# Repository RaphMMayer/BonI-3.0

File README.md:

# BonI 3.0
Mobile platform for sensory feedback via bone conduction.

The Project gives the PCB, Embedded SW and the API to drive the device via Bluetooth/Wifi.
## Table of Content
* [The PCB](#the-pcb)
  * [Two Layer PCB](#two-layer-pcb)
    * [Components](#components)
    * [Modifications](#modifications)
    * [Connection of the PCB](#connection-of-the-pcb)
    * [Programming and Operation of the PCB](#programming-and-operation-of-the-pcb)
    * [Debugging of the PCB](#debugging-of-the-pcb)
    * [Files](#files)
  * [Four Layer PCB](#four-layer-pcb)
  
* [Schematic](#schematic)
  * [The MCU](#the-mcu)
    * [MCU Pin Connections](#mcu-pin-connections)
  * [Frequency Generator](#frequency-generator)
    * [Frequency Generator Pin Connections](#frequency-generator-pin-connections)
    * [Programming the Frequency Generator](#programming-the-frequency-generator)

## The PCB
### Two Layer PCB:
The two layer PCB is designed as a prototype to our system. The PCB is a two layer board with a poured common ground on the bottom plane for both analogue and digital circuitry. Power traces and signal traces are located mostly on the top plane. With two mounting holes at the side of the PCB it is intended to be contained in the designed box. The PCB is fabricated and assembled by PCBWay.
#### Components:
- A power supply that can regulate 5V input into 3.3V and 5V. The 5V can be sourced from the programmer pins.
- ESP32 as the microcontorller.
- Three AD5932 ICs to generate frequencies.
- Three AD5970 digital potentiometers ICs for controlling the amplitude. 
- Three NCS2211 class AB amplifier ICs.
#### Modifications:
Being the first prototype of our project the PCB is heavily modified.
In order for the PCB to operate normally:
- The unconnected side of resistor C1 needs to be connected to ground.
- One of the unconnected pins of SW1 needs to be connected to ground.
- upper pads of C14 and C15 needs to be connected to provide power to function generators.
- R7, R11, R15, R19, R22 and R25 needs to be desoldered for the correct operation of SPI communications.
- 20K 0402 resistors need to be soldered at R20, R23 and R26 for the amplifier to work.
- The USB footprint J1 is left unused and is not intended to be used.
- Solder 2.56mm connecters to top pin of J1 and the square pin of J1, they are respectively the ground and +5 power supply for the PCB.
#### Connection of the PCB:
The PCB uses 2.56mm connectors for its programming pins and transducer signal output. 2.56mm female jumper headers should be used for proper connection to the system.
The battery port uses standard JST connenctors to fit with most lithium ion batteries.
#### Programming and Operation of the PCB:
The prototype is programmed with Arduino IDE. To program the PCB properly, the following instructions must be followed:
1. Connect TP12 and TP18 to ground. This allows ESP32 to be working in bootloading mode and allows for 3.3V flashing voltage. Failing to do so will result in flash read error.
2. Set the uploading speed to 115200 or above, it will not work with 921600.
3. When uploading the code press and hold SW2, wait until `connecting....`shows up, press and release SW1. This put ESP into flashing mode. Failing to do so will result in `A fatal error occurred: Failed to connect to ESP32: Timed out waiting for packet header`.
4. When it is uploading the code SW2 can now be released.
5. After uploading, `Hard resetting via RTS pin` should be observed,press the SW1 again to reset and boot the program. 
6. Now TP12 and TP18 can be lifted from ground to allow the pins from the MCU to operate as normal I/O pins, but TP18 should be connected to ground when trying to reboot the MCU.
#### Debugging of the PCB:
If encountered any problem, test points near the MCU are available for ruling out errors and faulty circuits.
| Test Point No. |  Net Name | Description |
|----|----|----|
|TP1|CTRL3| The transition from low to high at this pin enable the output of bottom function generator after it being reprogrammed |
|TP2|STANDBY3| Toggle to high to disable the bottom function generator|
|TP3|CTRL2| The transition from low to high at this pin enable the output of middle function generator after it being reprogrammed |
|TP4|CTRL1| The transition from low to high at this pin enable the output of top function generator after it being reprogrammed|
|TP5|STANDBY1|Toggle to high to disable the top function generator|
|TP6|STANDBY2|Toggle to high to disable the middle function generator|
|TP7|SPI1CLK|This pin should provide the clock to all the SPI devices|
|TP8|No connection|Don't Bother|
|TP9|ENABLE1|Toggle to high to turn off the top amplifier(May not work)|
|TP10|ENABLE2|Toggle to high to turn off the middle amplifier(May not work)|
|TP11|SPI1MOSI|This pin should transmit data to all the SPI devices|
|TP12|FSYNC2| This is the slave select pin for the middle function generator, when toggled low it allows the middle function generator to receive data from the MCU|
|TP13|FSYNC3| This is the slave select pin for the bottom function generator, when toggled low it allows the bottom function generator to receive data from the MCU|
|TP14|ENABLE3| Toggle to high to turn off the bottom amplifier(May not work) |
|TP15|SYNC3|This is the slave select pin for the bottom digital potentiometer, when toggled low it allows the bottom digital potentiometer to receive data from the MCU|
|TP16|FSYNC1|This is the slave select pin for the top function generator, when toggled low it allows the top function generator to receive data from the MCU|
|TP17|SYNC1|This is the slave select pin for the top digital potentiometer, when toggled low it allows the top digital potentiometer to receive data from the MCU|
|TP18|SYNC2|This is the slave select pin for the middle digital potentiometer, when toggled low it allows the middle digital potentiometer to receive data from the MCU|
#### Files
All the PCB designs are done in KiCad. The PCB files of the two layer board can be found in the repository. The design is modified so that the aforementioned modifications does not need to be carried out for the two layer board PCB design if the desgin is to be printed in manufactures.
### Four Layer PCB
## Schematic
Both the original and updated version of the schematic can be found in the repository. The schematic is drawn in KiCad. On the first page, there is the frequency generator, amplifier and digital potentiometer. On the second page, there is the MCU and power section. 
### The MCU:
The MCU used in ths project is ESP32-WROOM-32D(4MB)([datasheet](https://www.espressif.com/sites/default/files/documentation/esp32-wroom-32_datasheet_en.pdf)). It mainly serves for communication between the GUI and the frequency generator. Apart from a few pins used for programming, most of the pins are used to communicate with the frequency generators, digital potentiometers and the amplifier.
The MCU communicates with frequency gnerators and digital potentiometers using SPI protocol. The ESP32 has two SPI channels available, and only one of them is utilized. Below are the connections from the MCU.
#### MCU Pin Connections
|Pin No.|Pin Name|Descriptions|
|----|----|----|
|1,15,38|GND|Connected to ground|
|2|DVDD|Power of ESP32, a well regulated 3.3V source is needed|
|3|EN|Reset pin of ESP32, it is connected to a switch, push to reboot the system|
|4|SENSOR_VP|Not used|
|5|SENSOR_VN|Not used|
|6,7,8|IO34 IO35 IO32|Not used|
|9,14,27|IO33 IO12 IO16|SYNC3, SYNC2 and SYNC1, slave select for digital potentiometer|
|10,16,28|IO25 IO13 IO17|ENABLE3, ENABLE2 and ENABLE1, used for turning on and off the amplifier|
|11,23,29|IO26 IO15 IO5|STANDBY3, STANDBY2 and STANDBY1, used for turning on and off the frequency generator|
|12,24,31|IO27 IO2 IO19|FSYNC3, FSYNC2 and FSYNC1, slave select for frequency generator|
|13,26,33|IO14 IO4 IO21|CTRL3, CTRL2 and CTRL1, update the output of the frequency generator|
|17,18,19,20,21,22|SDO SDI SHD SWP SCK SCS| Not used|
|25|IO0| Connected to a switch, hold low and press EN to enter bootloading|
|30|IO18|SPICLK used to synchronize all the SPI devices|
|32|NC|Do not connect|
|34,35|RXD0 TXD0| Serial port used for prgramming, connected to programming pins.|
|36|IO22|Not used.|
|37|IO23|SPIMOSI Used to send SPI data from the MCU|
### Frequency Generator
The frequency generator used in this project is AD5932([datasheet](https://www.analog.com/media/en/technical-documentation/data-sheets/AD5932.pdf)). This is a direct digital synthesis IC that uses SPI communication. It has 24 bits resolution frequency generation derived from the master clock (MCLK) fed in to it. In other words, the frequency it can output can be calculated by MCLK/2^24. We use a MCLK of 32.768kHz for our application. This means we have a frequency range from 0Hz to 32.768kHz with a frequency resolution of 0.00195Hz. It can produce sinusoidal, triangle and square waves at a fixed amplitude of 580 mV peak to peak. The IC also have auto frequency sweeping fucntion, which we are not intended to use in our project. To program the IC properly the MCU must write to AD5932 using SPI communication. 
#### Frequency Generator Pin Connections
|Pin No.|Pin Name|Descriptions|
|----|----|----|
|1|COMP|Decoupled to AVDD|
|2|AVDD|Analog supply (3.3V)|
|3|DVDD|Digital supply (3.3V)|
|4|CAP/2.5V|Decoupled to ground, decoupled to DVDD if DVDD is less than 2.5V|
|5|DGND|Digital Ground|
|6|MCLK|Input master clock from here, connected to SG-3030CM clock generator([datasheet](#https://www5.epsondevice.com/en/products/crystal_oscillator/sg3030cm.html))|
|7|SYNCOUT|Not connected, will output a signal after a frequency sweep(not tested)|
|8|MSBOUT|Not connected, square wave output can be yielded from this port|
|9|Interrupt|Not connected, used to interrupt a frequency sweep|
|10|CTRL|This pin needs to be toggled from low to high to output the frequency written to the frequency generator|
|11|SDATA|The MOSI pin of the device, receive data from SPI master|
|12|SCLK| The SPICLK pin of the device, receive clock from MCU to synchronize the bit transmision|
|13|FSYNC| The slave select pin of the device, pulled low to allow receiving of data|
|14|STANDY| Pull the pin high to disable the frequency generator|
|15|AGND|Analog ground|
|16|VOUT|The output pin for both triangle and sinusoidal wave, switch between the two in software|
#### Programming the Frequency Generator
To program the frequency generator AD5932, a 12 bit data must be written to the 4 bit register with mode 3 SPI communication(CPOL=1 CPHA=0). The following table shows the register used and the data transmitted to each register in the program where the first four bits represent the register written to and the rest are the data bits:
|Function|Data(Binary)|Data(Hexadecimal)|Description|
|--------|---|-----|---|
|Initialize:|	0	0	0	0 1 1 1 0	1 1	0	1	0	0	1	1|0x0ED3|	bit 11 set to one so that both	LSB and MSB are needed to change the outputfrequency. Bit 10 set to 1 to Enable DAC. Bit 9 set to 1	to select sinusoidal wave (0 for triangle wave).	Bit 8 set to 0 for N=no square output(1 for square output from MSBout)	Bit 5 set to 0 to enable automatic frequecny sweep(Don't matter). Bit 3 only matter if bit 2 is set to 1.	Bit 2 set to 0 to not have a pulse at end of sweep(not needed)|	
|No of increment|		0	0	0	1	0	0	0	0	0	0	0	0	0	0	1	0	|0x1002|The bit transmitted should be set to decimal equivalent of 2 for the minimum number of frequency increments(not needed in our case)|
|Period of increment|0	1	1	0	x	x	x	x	x	x	x	x	x	x	x	x|	0x63E8|	Don't care if no frequency sweeping is needed. It is initailized to 1000/MCLK=0.03s|
Frequency Increment LSB|0	0	1	0	0	0	0	0	0	0	0	0	0	0	0	0|0x2000|		Set to 0 if not needed|
Frequency Increment MSB|0	0	1	1	0	0	0	0	0	0	0	0	0	0	0	0	|0x3000|Set to 0 if not needed|																
Start Frequency LSB|1	1	0	0	0	0	0	0	0	0	0	0	0	0	0	0|0xC000|	Set the frequency output. Divide the desired frequency by 0.00195 to yield the data bits.|
Start Frequency MSB	|1	1	1	0	0	0	0	0	0	0	0	0	0	0	0	0|0xD000|Set the frequency output. Divide the desired frequency by 0.00195 to yield the data bits.|

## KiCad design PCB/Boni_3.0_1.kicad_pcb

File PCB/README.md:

# BonI PCB
Included are KiCad files for PCB design, Gerber files as well as bill of materialthat was sent to the manufacturers. The old version of two layer PCB need modifications to be functioning properly. The new version of the two layer PCB is also in the repository.

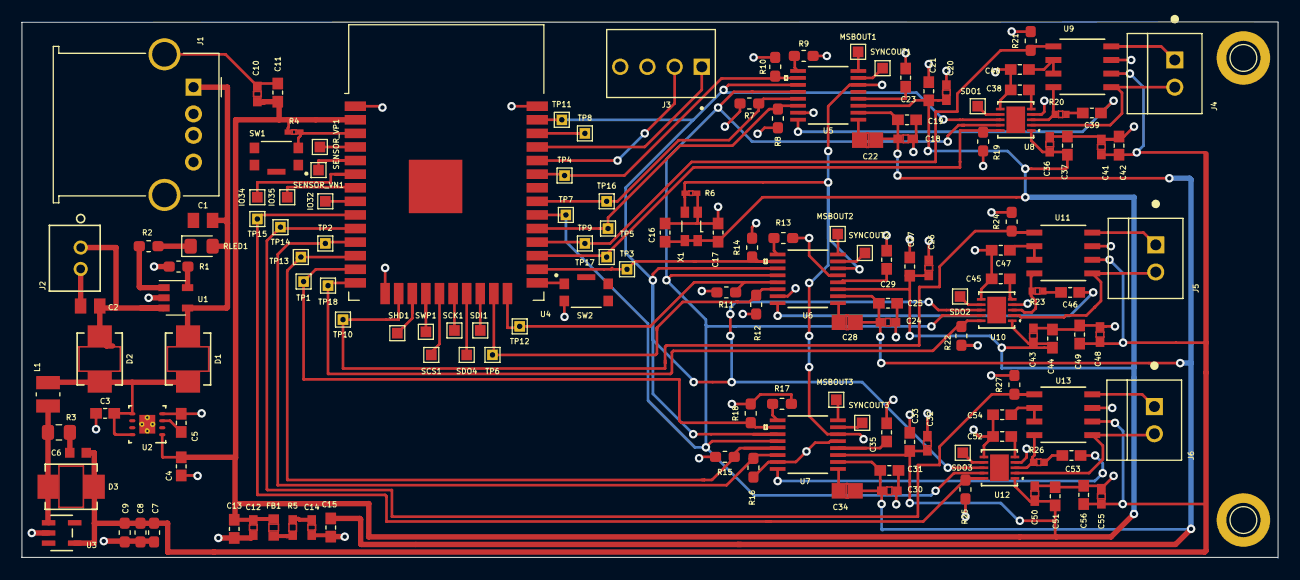
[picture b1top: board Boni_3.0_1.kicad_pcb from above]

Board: 2 copper layers, 117.4 x 50.1 mm, 151 parts (0 on the bottom side), 87 nets.

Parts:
C1, C2: 4.7uF; CAPC2012X95N
C3, C11, C13, C15, C16, C17, C19, C21, C23, C25, C27, C29, C31, C33, C35, C37, C40, C42, C44, C47, C49, C51, C54, C56: 0.1uF; CAPC1608X90
C4, C5, C38, C39, C45, C46, C52, C53: 1uF; CAPC1608X90
C6: 1000pF; CAPC1608X90N
C7, C8, C9: 10uF; C_0603_1608Metric_Pad1.05x0.95mm_HandSolder
C10, C12, C14, C18, C20, C24, C26, C30, C32, C36, C41, C43, C48, C50, C55: 10uF; GRM188R60J106ME84D
C22, C28, C34: 0.01uF; C0805C103J5RAC7210
D1, D2, D3: MBRS340T3G; MBRS130LT3G
Drill1, Drill1#2: Pin_D1.0mm_L10.0mm
FB1: 600Ohm@100MHz; MH1608-601Y
IO32, IO34, IO35: TestPoint; TestPoint_Pad_1.0x1.0mm
J1: USBminiAB; USB_A_Molex_67643_Horizontal
J2: B2B-PH-K-SLFSN
J3: PROG; TE_3-647116-4
J4, J5, J6: Conn_01x02_Male; TE_5-103669-1
L1: 2.2uH; INDC2520X120N
MSBOUT1, MSBOUT2, MSBOUT3: TestPoint; TestPoint_Pad_1.0x1.0mm
R1: 2k; R_0603_1608Metric_Pad1.05x0.95mm_HandSolder
R2: 470; R_0603_1608Metric_Pad1.05x0.95mm_HandSolder
R3: 5; R_0805_2012Metric_Pad1.15x1.40mm_HandSolder
R4, R6: 10k; 10kr
R5: 1.6; 1.6r
R7, R8, R9, R10, R11, R12, R13, R14, R15, R16, R17, R18, R19, R21, R22, R24, R25, R27: 10k; R_0603_1608Metric_Pad1.05x0.95mm_HandSolder
R20, R23, R26: 25k; 20kr
RLED1: SML-D12M1WT86; LED_0805_2012Metric_Pad1.15x1.40mm_HandSolder
SCK1: TestPoint; TestPoint_Pad_1.0x1.0mm
SCS1: TestPoint; TestPoint_Pad_1.0x1.0mm
SDI1: TestPoint; TestPoint_Pad_1.0x1.0mm
SDO1, SDO2, SDO3, SDO4: TestPoint; TestPoint_Pad_1.0x1.0mm
SENSOR_VN1: TestPoint; TestPoint_Pad_1.0x1.0mm
SENSOR_VP1: TestPoint; TestPoint_Pad_1.0x1.0mm
SHD1: TestPoint; TestPoint_Pad_1.0x1.0mm
SW1: SW_Push; SW_KMR421GULCLFS
SW2: SW_DPST_x2; SW_KMR421GULCLFS
SWP1: TestPoint; TestPoint_Pad_1.0x1.0mm
SYNCOUT1, SYNCOUT2, SYNCOUT3: TestPoint; TestPoint_Pad_1.0x1.0mm
TP1: CTRL3; TestPoint_THTPad_1.0x1.0mm_Drill0.5mm
TP2: STANDBY3; TestPoint_THTPad_1.0x1.0mm_Drill0.5mm
TP3: CTRL2; TestPoint_THTPad_1.0x1.0mm_Drill0.5mm
TP4: CTRL1; TestPoint_THTPad_1.0x1.0mm_Drill0.5mm
TP5: STANDBY1; TestPoint_THTPad_1.0x1.0mm_Drill0.5mm
TP6: STANDBY2; TestPoint_THTPad_1.0x1.0mm_Drill0.5mm
TP7: SPI1CLK; TestPoint_THTPad_1.0x1.0mm_Drill0.5mm
TP8: IO22; TestPoint_THTPad_1.0x1.0mm_Drill0.5mm
TP9: ENABLE1; TestPoint_THTPad_1.0x1.0mm_Drill0.5mm
TP10: ENABLE2; TestPoint_THTPad_1.0x1.0mm_Drill0.5mm
TP11: SPIMOSI; TestPoint_THTPad_1.0x1.0mm_Drill0.5mm
TP12: FSYNC2; TestPoint_THTPad_1.0x1.0mm_Drill0.5mm
TP13: FSYNC3; TestPoint_THTPad_1.0x1.0mm_Drill0.5mm
TP14: ENABLE3; TestPoint_THTPad_1.0x1.0mm_Drill0.5mm
TP15: SYNC3; TestPoint_THTPad_1.0x1.0mm_Drill0.5mm
TP16: FSYNC1; TestPoint_THTPad_1.0x1.0mm_Drill0.5mm
TP17: SYNC1; TestPoint_THTPad_1.0x1.0mm_Drill0.5mm
TP18: SYNC2; TestPoint_THTPad_1.0x1.0mm_Drill0.5mm
U1: MCP73831-2-OT; SOT-23-5
U2: TPS73733QDRBRQ1
U3: TPS613222ADBVR
U4: ESP32D; ESP32-WROOM-32
U5, U6, U7: AD5932; AD5932YRUZ
U8, U10, U12: AD5270; AD5270BCPZ-20-RL7
U9, U11, U13: NCS2211
X1: SG-3030CM; Oscillator_SMD_SeikoEpson_SG3030CM

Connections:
+5V: C6.2, C7.1, C8.1, C9.1, C41.1, C42.1, C48.1, C49.1, C55.1, C56.1, D3.1, U3.4, U9.6, U11.6, U13.6
AVDD: C14.1, C15.1, C18.1, C19.1, C22.2, C24.1, C25.1, C28.2, C30.1, C31.1, C34.2, R5.1, U5.2, U6.2, U7.2
CTRL1: R10.1, TP4.1, U4.33, U5.10
CTRL2: R14.1, TP3.1, U4.26, U6.10
CTRL3: R18.1, TP1.1, U4.13, U7.10
DVDD: C4.2, C10.1, C11.1, C12.1, C13.1, C16.1, C17.1, C20.1, C21.1, C26.1, C27.1, C32.1, C33.1, C36.1, C37.1, C43.1, C44.1, C50.1, C51.1, FB1.2, R4.1, U2.1, U4.2, U5.3, U6.3, U7.3, U8.1, U10.1, U12.1, X1.1, X1.4
ENABLE1: R21.1, TP9.1, U4.28, U9.1
ENABLE2: R24.1, TP10.1, U4.16, U11.1
ENABLE3: R27.1, TP14.1, U4.10, U13.1
FSYNC1: R7.1, TP16.1, U4.31, U5.13
FSYNC2: R11.1, TP12.1, U4.24, U6.13
FSYNC3: R15.1, TP13.1, U4.12, U7.13
GND: C1.2, C2.2, C3.2, C4.1, C5.1, C7.2, C8.2, C9.2, C10.2, C11.2, C12.2, C13.2, C14.2, C15.2, C16.2, C17.2, C18.2, C19.2, C20.2, C21.2, C23.2, C24.2, C25.2, C26.2, C27.2, C29.2, C30.2, C31.2, C32.2, C33.2, C35.2, C36.2, C37.2, C38.2, C40.2, C41.2, C42.2, C43.2, C44.2, C45.2, C47.2, C48.2, C49.2, C50.2, C51.2, C52.2, C54.2, C55.2, C56.2, J1.5, J2.2, J3.3, R1.2, R6.2, R7.2, R8.2, R9.2, R10.2, R11.2, R12.2, R13.2, R14.2, R15.2, R16.2, R17.2, R18.2, R19.2, R21.2, R22.2, R24.2, R25.2, R27.2, SW1.1, SW2.2, U1.2, U2.4, U2.9, U3.2, U4.1, U4.15, U4.38, U4.39, U5.5, U5.15, U6.5, U6.15, U7.5, U7.15, U8.4, U8.6, U9.7, U10.4, U10.6, U11.7, U12.4, U12.6, U13.7, X1.2
unnamed: C2.1, D2.2, J2.1, U1.3
unnamed: C3.1, D1.1, D2.1, L1.1, U2.5, U2.8
unnamed: C5.2, U2.3
unnamed: C6.1, R3.1
unnamed: C22.1, U5.1
unnamed: C23.1, U5.4
unnamed: C28.1, U6.1
unnamed: C29.1, U6.4
unnamed: C34.1, U7.1
unnamed: C35.1, U7.4
unnamed: C38.1, U8.5
unnamed: C39.1, R20.2
unnamed: C40.1, U9.2, U9.3
unnamed: C45.1, U10.5
unnamed: C46.1, R23.2
unnamed: C47.1, U11.2, U11.3
unnamed: C52.1, U12.5
unnamed: C53.1, R26.2
unnamed: C54.1, U13.2, U13.3
unnamed: D3.2, L1.2, R3.2, U3.1
unnamed: FB1.1, R5.2
unnamed: IO32.1, U4.8
unnamed: IO34.1, U4.6
unnamed: IO35.1, U4.7
unnamed: J3.1, U4.35
unnamed: J3.2, U4.34
unnamed: J4.1, U9.8
unnamed: J4.2, U8.2, U9.5
unnamed: J5.1, U11.8
unnamed: J5.2, U10.2, U11.5
unnamed: J6.1, U13.8
unnamed: J6.2, U12.2, U13.5
unnamed: MSBOUT1.1, U5.8
unnamed: MSBOUT2.1, U6.8
unnamed: MSBOUT3.1, U7.8
unnamed: R1.1, U1.5
unnamed: R2.1, RLED1.1
unnamed: R2.2, U1.1
unnamed: R4.2, SW1.2, U4.3
unnamed: R6.1, U5.6, U6.6, U7.6, X1.3
unnamed: R9.1, U5.9
unnamed: R13.1, U6.9
unnamed: R17.1, U7.9
unnamed: R20.1, U8.3, U9.4
unnamed: R23.1, U10.3, U11.4
unnamed: R26.1, U12.3, U13.4
unnamed: SCK1.1, U4.20
unnamed: SCS1.1, U4.19
unnamed: SDI1.1, U4.22
unnamed: SDO1.1, U8.7
unnamed: SDO2.1, U10.7
unnamed: SDO3.1, U12.7
unnamed: SDO4.1, U4.21
unnamed: SENSOR_VN1.1, U4.5
unnamed: SENSOR_VP1.1, U4.4
unnamed: SHD1.1, U4.17
unnamed: SW2.1, U4.25
unnamed: SWP1.1, U4.18
unnamed: SYNCOUT1.1, U5.7
unnamed: SYNCOUT2.1, U6.7
unnamed: SYNCOUT3.1, U7.7
unnamed: TP8.1, U4.36
SIN1: C39.2, U5.16
SIN2: C46.2, U6.16
SIN3: C53.2, U7.16
SPI1CLK: TP7.1, U4.30, U5.12, U6.12, U7.12, U8.9, U10.9, U12.9
SPI1MOSI: TP11.1, U4.37, U5.11, U6.11, U7.11, U8.8, U10.8, U12.8
STANDBY1: R8.1, TP5.1, U4.29, U5.14
STANDBY2: R12.1, TP6.1, U4.23, U6.14
STANDBY3: R16.1, TP2.1, U4.11, U7.14
SYNC1: R19.1, TP17.1, U4.27, U8.10
SYNC2: R22.1, TP18.1, U4.14, U10.10
SYNC3: R25.1, TP15.1, U4.9, U12.10
Vusb: C1.1, D1.2, J1.1, RLED1.2, U1.4

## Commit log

2020-10-19 Rename PCB/Boni_3.0_1.kicad_pcb to PCB/OldVersion/Boni_3.0.kicad_pcb
2020-10-19 Rename PCB/Boni3.0_1/Boni_3.0_1-B_Cu.gbl to PCB/OldVersion/GerberFiles/Boni_3.0-B_Cu.gbl
2020-10-19 Rename Code/Functions/BonI1FG.ino to Code/Functions/TestingExample/BonI1FG.ino
2020-10-26 add interface
2020-10-26 modified the interface
2020-10-26 Rename BonI3.0WiFi.ino to BonI3.0.ino
2020-10-28 Update TestScript.m
    Fixed bugs

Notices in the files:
parts and their libraries:
Copyright 2016 Accelerated Designs. All rights reserved.
